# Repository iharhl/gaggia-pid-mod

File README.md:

# Gaggia PID mod

This project adds PID temperature control to my Gaggia Classic
espresso machine. Inspired by similar DIY efforts, I wanted to
challenge myself by designing and implementing the modification
entirely from scratch.

By default, Gaggia uses thermostat-based (on/off) temperature control,
which has noticed deviations from the ideal temperature. A PID controller
offers more precise and consistent temperature regulation compared to the
stock thermostat, which helps improve shot quality.

---

**Update Jul 2026:** I decided to create a custom "carrier" PCB which is more
compact, robust, and makes wiring more organized. Instead of using the same
microcontroller board, I switched from Pi Pico to RP2040-Zero (has the same MCU).
This readme file was updated accordingly. See the new control box below.

---

## Table of contents

1. [Hardware](#hardware)
   - [Temperature sensing](#temperature-sensing)
   - [Power switching](#power-switching)
   - [Microcontroller board](#microcontroller-board)
   - [Additional hardware](#additional-hardware)
   - [Bonus: Brew timer](#bonus-brew-timer)
2. [Software](#software)
   - [Temperature measurement](#temperature-measurement)
   - [PID controller](#pid-controller)
   - [Relay control](#relay-control)
   - [Error handler](#error-handler)
   - [Display](#display)
   - [Pump](#pump)
   - [Other](#other)
   - [Helper tools](#helper-tools)
3. [Results](#results)
   - [Calibration](#calibration)
   - [Final assembly (old)](#final-assembly-old-pi-pico-version)
   - [Final assembly (new)](#final-assembly-new-rp2040-zero-version)
   - [Taste Test](#taste-test)
4. [Resources](#resources)

## Hardware

The Gaggia machine regulates temperature using basic thermostat, which
functions as a switch that cuts off power when the water temperature
exceeds its rated threshold – 107°C for brewing. However, this approach
results in a sluggish system response. Once the temperature reaches the
cutoff point, it tends to slowly oscillate around the target, deviating
by several degrees. This rudimentary control method lacks the precision
needed for accurate temperature regulation.

To achieve more precise control, we need to continuously monitor the
water temperature and adjust the power to the heating element dynamically
based on real-time measurements. This allows for smoother and more
accurate temperature control.

To implement such a system, following components are required:

- Temperature sensor
- Power switch
- Microcontroller board

### Temperature sensing

The application requires measuring relatively short-term changes in
temperature over a wide range (~0°C to 200°C) with high accuracy
(better than ±0.5°C).

A common use case that fits these requirements is temperature control
in a water heater, where RTD (Resistance Temperature Detector) sensors
are frequently used. For this purpose, a Pt100 RTD sensor was
selected. It meets the accuracy and range specifications and is readily
available with an M4 adapter suitable for mounting to a boiler.

However, achieving accurate temperature readings from an RTD sensor
requires a precise analog-to-digital converter (ADC) and amplification.
Fortunately, this problem has been effectively solved with the MAX31865
– a user-friendly resistance-to-digital converter optimized for platinum
RTDs like the Pt100. With the MAX31865, you simply connect the sensor,
configure the device, and it provides accurate digital temperature
readings.

Adafruit offers high-quality breakout boards based on the MAX31865
chip, along with comprehensive documentation and example code. The sensor
itself I found on AliExpress with integrated M4 screw and of 3-wire type.
See examples of MAX31865 and RTD sensor below.

### Power switching

With the thermostat removed, an alternative method is needed to switch
the power on and off. A mechanical relay is the most straightforward
option and probably could suffice.

However, solid-state relays (SSRs) are often preferred in high-power
scenarios for several practical reasons. While both options are capable
of handling the load, SSRs offer significant advantages:

- Silent operation: unlike mechanical relays that produce an audible
"click" during switching, SSRs operate silently.

- Longer lifespan: SSRs have no moving parts, which drastically reduces
mechanical wear and increases operational longevity, particularly under
frequent switching conditions.

- Faster switching: the ability of SSRs to switch much faster than
mechanical relays.

- Reduced electrical noise: SSRs can be zero-crossing triggered, 
minimizing electrical noise and transients during switching.

Given these benefits, I opted for a commonly available 40A-rated SSR.
These are widely used, reliable, and relatively inexpensive, making
them a solid choice for high-power switching applications. According
to the specifications, the control method is listed as zero-crossing.
The SSR model is shown on the image below.

### Microcontroller board

There are many microcontrollers that could handle this task, as long as
they provide enough GPIO pins, support both I2C and SPI communication,
and have sufficient memory resources.

I had a Raspberry Pi Pico on hand that I hadn’t worked with before, so
I decided to use it as the microcontroller for this project.

**Update Jul 2026:** for a carrier PCB, I switch the board to RP2040-Zero –
both are supported now.

### Additional hardware

The components mentioned above cover the core functionality, but a few
important elements are still missing.

First, the Raspberry Pi Pico needs a power source. While it can be
powered via USB during development and debugging, this is only a
temporary solution. For a standalone setup, an AC/DC power supply is
required to draw power from the machine itself. I found a small module
on AliExpress that outputs up to 600mA at 5V, which is more than
sufficient for powering the Pico and a few peripherals.

The module turned out to be of poor quality. Its output was quite noisy,
and there were grounding issues. While most components in the system
would tolerate these, the MAX31865 is considerably more sensitive. As a
result, it frequently reported faults during temperature readings.

Fortunately, I had an AC/DC power supply from my broken speakers on hand,
so I used it for this project. Adding a pair of decoupling capacitors to
its output (100µF electrolytic and 0.1µF ceramic) resulted in a very smooth
voltage curve. However, the output measured at ~6V, which is around absolute
maximum rating of the on-board regulator. I used a diode to introduce a
voltage drop. Additionally, the power supply discharged very slowly after
the power was cut off. To address this, I soldered in a low-value bleed
resistor to speed up the discharge. In the end, the Pico is powered via
the VSYS pin with a stable ~5.1V supply.

Second, we need a way to monitor the machine's temperature in real
time. A small display would be a practical addition for this purpose,
allowing for quick and convenient observation of temperature readings.
I came across a very nice 1.5" 128×128 grayscale OLED display from
Adafruit, which includes comprehensive documentation.

### Bonus: Brew timer

Regarding the hydraulics upgrade, one of the most popular modifications
is the dimmer mod. This approach controls the pump flow by chopping the
AC supply using a phase-angle dimmer circuit. While it allows for
pressure profiling, it is worth noting that this method can lead to
increased wear on the pump, as this vibration pump is not designed to
operate under such conditions.

A simpler alternative is pump time control. By interrupting power to the
pump, you can implement programmable shot timing – effectively automating
brew durations without modifying flow or pressure directly. All that is
required for this mod is a relay board and some wiring to detect when the
brew button has been pressed.

Since I dragged this project out for too long, I ultimately decided
to skip the relay part of the mod – it would not have made a meaningful
difference for my use case anyway. However, I wired the brew button
to the Pico.

On the EU model of the machine, there is a switch-off board
included. Wires on the left side of the brew switch (in my case, blue and
green ones) are connected to it so that the power-off timer is reset
when brewing. I removed these two wires and shorted them (to make the
board think the brew is on at all time). The available connections can
now be used to detect when the button is pressed.

## Software

Since the Pico board was chosen, the MCU provides plenty of resources to
write a somewhat abstract code :)

To make the implementation easier to write and more readable, I followed
an OOP approach. Each component with a specific purpose is encapsulated
in its own class. For example, each communication protocol (I2C/SPI) is
implemented as a separate class. The drivers for external components,
such as MAX31865 and the OLED display, are also organized into classes
that utilize the I2C or SPI class instances for communication.

Here is a high-level overview of the software:

### Temperature measurement

Temperature measurements are obtained via the MAX31865 chip, which
uses SPI for communication. Hence, the SPI driver class was implemented.
Due to specific timing requirements of the MAX31865, slight modification
were done to the native Pico SDK SPI calls. The details are available in 
the implementation file – [src/spi.cpp](src/spi.cpp). Below are examples of
SPI read and write operations captured with a logic analyzer:

The MAX31865 driver implements the chip-specific logic
and utilizes the SPI class instance for communication. Details can be
found here – [src/max31865.cpp](src/max31865.cpp)

### PID controller

Not much to explain here – a PID temperature controller logic is
encapsulated within the PID class. The implementation is minimal, only
includes basic P-I-D action, no filtering, and includes integral
anti-windup to prevent the accumulation of integral action (which is 
important in such slow control systems).

The PID compute method takes temperature setpoint and the measurement as
inputs (error is calculated inside), and outputs the PWM percentage (duty
cycle). Implementation can be found here –
[src/pid.cpp](src/pid.cpp)

### Relay control

The SSR is controlled via PWM, hence the logic is put into PWM class.
The small problem here is that the control systems is quite slow
leading to a long PWM period, too long to be controlled using Pico's
dedicated PWM peripherals. Therefore, the PWM logic was implemented
via combination of timer peripheral and GPIO actions. Check details here –
[src/pwm.cpp](src/pwm.cpp)

<small>

> An interesting consideration here is how much power is delivered to the
heating element during each PWM period. Here's what I mean: suppose
the PID controller outputs a 10% duty cycle. Depending on the length
of the PWM period, this 10% can represent different chunks of time –
for example, 0.11 sec.
> 
> In the EU, the AC mains frequency is 50 Hz, meaning each full AC cycle
lasts 20 ms. However, 0.11 sec is not an even multiple of
the AC period (0.11 / 0.02 = 5.5 cycles), so the PWM period slices
through the AC waveform at arbitrary points. As a result, depending on
exactly where in the AC cycle the PWM turns on or off, the average power
delivered can fluctuate between periods.
>
> To achieve more consistent power delivery, it is desirable to align the
PWM period so that it is an integer multiple of the AC cycle period – for
example, setting the PWM period to 2 seconds (100 full AC cycles). This
way, for any given duty cycle, the on-time will always correspond to a
whole number of complete AC periods, rather than cutting through the AC
waveform at arbitrary points. As a result, the average power delivered
becomes more predictable and stable.
>
> Of course, there are some caveats here, and the topic can get quite
technical – including issues like the non-ideal nature of mains
frequency, inrush current when switching at AC peaks, and other
electrical nuances. That said, these details are not critical for this
particular system in my opinion, especially since the SSR I chose
features zero-crossing control. Still, it's an interesting topic to
explore.

</small>

### Error handler

As this mod is not exactly stress-tested, some form of error handler was
logical to implement.

The approach I took was straightforward: during a cycle, the system
checks whether input conditions are met. If a condition fails and the
associated error has a higher priority than previously stored error, the
system stores the new error code. At the end of the loop, the following
actions are taken:

- Disable PWM output if the error is severe enough.

- Display the current error code. If no error is present, reset the
error status and re-enable the PWM.

Possible error codes are summarized in the table below:

| Error Code | Error Context | Description                                                                           |
|------------|---------------|---------------------------------------------------------------------------------------|
| P0         | Protection    | Watchdog just rebooted the MCU (execution will continue shortly)                      |
| P1         |               | VSYS ADC is not configured correctly                                                  |
| P2         |               | Over voltage detected on VSYS                                                         |
| P3         |               | Under voltage detected on VSYS                                                        |
| P4         |               | Boiler too hot (higher than typical steaming temperature)                             |
| P5         |               | Machine was running for too long                                                      |
| C0         | Communication | Error occurred during I2C communication                                               |
| C1         |               | SPI device seems to be disconnected                                                   |
| S0         | Sensing       | MAX31865 reports under/overvoltage                                                    |
| S1         |               | MAX31865 reports RTD input voltage is too low                                         |
| S2         |               | MAX31865 reports reference input voltage is too high                                  |
| S3         |               | MAX31865 reports reference input voltage is too low                                   |
| S4         |               | MAX31865 reports RTD resistance is lower than the configured low threshold            |
| S5         |               | MAX31865 reports RTD resistance is higher than the configured high threshold          |
| S6         |               | Abnormal / not realistic boiler temperature (without MAX31865 reporting faults)       |
| HI         | User info     | Warning to the user that boiler temperature above setpoint (does not disable the PWM) |
| LO         |               | Warning to the user that boiler temperature below setpoint (does not disable the PWM) |
| OK         |               | Boiler temperature close to setpoint and no errors detected                           |

Check the implementation here – [src/error.cpp](src/error.cpp)

### Display

The OLED display uses SSD1327 driver chip with I2C as the default
communication protocol. I chose to structure the display logic in
3 layers:

- The I2C driver class handles communication. The default timings in the
Pico SDK were sufficient, so no modifications were necessary. Check 
here – [src/i2c.cpp](src/i2c.cpp)

- The SSD1327 driver manages the logic for updating the display, such
as filling or clearing the screen, drawing specific regions, and more.
Implementation can be found here – [src/ssd1327.cpp](src/ssd1327.cpp)

- The GUI driver oversees the display layout, including how quickly the
display is updated and how individual numbers or letters correspond to
an actual pixel data. Source file – [src/gui.cpp](src/gui.cpp)

Image below shows the layout of 128x128 display:

It is split into three rows. These rows are:

1. Thermometer icon and three digit fields to show the temperature
of the boiler.
2. Status icon and two fields to show the status code. Error codes are 
represented as a letter and a number (except for HI/LO/OK status codes).
3. Cup icon and two digit fields to show the shot timer. When the brew
switch is pressed, the timer starts. After the button is released, the
timer remains visible for 5 seconds before automatically resetting to
zero. The cup icon changes if the brew timer is active.

Images below show examples of what can be displayed.

<small>

> All the icons, letters, and numbers were drawn by me using an online
> designer for pixel art – Pixilart. The original .pixil files, generated
> png images, etc. are stored in [docs/display/](docs/display)

</small>

### Pump

The pump logic is based on a simple state machine. When the brew button
is pressed, the normally closed (NC) relay remains inactive, allowing
the water to flow. After the programmed time elapses, the relay opens,
cutting the power to the pump. After the brew button is released by the
user, the relay returns to its default closed position. For details, see
– [src/pump.cpp](src/pump.cpp)

This setup enables precise shot timing without the need for manual
tracking of time. While I have not set up the relay part myself, I've
left the code in place.

The part of the code that is used though, is detection of brew button
presses. This enables real-time display of the shot extraction time.

### Other

Source code also includes:

- Clock class provides current uptime of the MCU in ms, sec, and min.
All the methods are static as the class does not need to be instantiated,
it just encapsulates the logic relevant to time. Check
[src/clock.cpp](src/clock.cpp)

- Led class controls the on-board LED. Same as clock, all methods are
static. Check [src/led.cpp](src/led.cpp)

- Vsys monitor class provides the ability to measure the voltage on VSYS line.
As the ADC handling is minimal in the software, I decided to not create a
separate class for it. Check [src/vses.cpp](src/vsens.cpp). **Update Jul 2026:**
custom PCB has a voltage divider, which PR2040-Zero uses to read VDC from
the AC/DC supply, instead of measuring VSYS line itself.

- Watchdog that reboots the MCU if it is not updated in a defined amount
of time. It has no class of its own, direct SDK calls are used.

- For debug and test data recording, custom print functions were
implemented. They communicate data over serial to a connected
computer. Check [src/myprint.h](src/myprint.h)

### Helper tools

To aid the development, I made several scripts which are stored in the
[tools/](tools) folder.

| Script          | Description                                                                     |
|-----------------|---------------------------------------------------------------------------------|
| flash.sh        | Build and flash the binary on the Pico or PR2040-Zero boards and print its size |
| listen.py       | Connect to serial port and record data transmitted from the Pico                |
| process-data.py | Parse and plot the temperature data recorded from serial                        |
| png-to-bytes.py | Convert png image into raw data to be displayed on the OLED                     |

## Results

### Calibration

To calibrate the PID, I began by recording performance data. The
graphs below show the final results I was able to achieve after some
calibration.

The boiler heat-up is quite smooth, reaching operating temperature in
about 100 seconds. The system seems slightly over damped, requiring some
effort to reach the final few degrees. Once at temperature, it oscillates
with a ±1°C deviation for a short while. Given the system's slow thermal
response, I consider this level of accuracy quite acceptable. By around
the 4-minute mark, the error narrows to about ±0.5°C and continues to
improve over time.

The result of a shot pull test is also shown below. During brewing, the
water temperature drops by almost 3°C. After, it overshoots by about
1.5°C but stabilizes relatively quickly, with full recovery achieved
within a minute.

Additionally, I tested how well my modification works with the stock
steam control. As expected, once the boiler was heated, I reset the
steam switch, and the temperature gradually decreased. After such a
prolonged (passive) cooling, the integral term accumulated significantly,
resulting in an initial temperature undershoot (visible at around the
600-second mark). However, within about one and a half minutes, the
controller compensated and returned the system to the setpoint.

While this is not a realistic usage scenario – doubt anyone would really
wait 10 minutes for the boiler to cool passively (while having the machine
on) – I conducted a more practical test next. After reaching steam
temperature, I manually dropped the temperature by flushing water. This
caused the temperature to fall below the setpoint, but the controller
responded quickly. Two factors contributed to the improved response:
first, the integral term had less time to accumulate error; second, the
steep drop triggered a strong derivative response. In this test, the
system recovered rapidly and stabilized efficiently.

Overall, the controller is stable, and the system's performance is more
than adequate for real-world use – substantially better than the stock
configuration. Although further PID tuning is possible, the current
setup delivers great results.

### Final assembly (old Pi Pico version)

The circuit diagram of the final assembly is shown below. It illustrates
how most of the components were wired together.

The photos below provide a rough overview of the assembly process. In
the first image, I have highlighted the main modification. Here is a
brief explanation of the numbered tags:

1. **Power Source** – Power is drawn from the machine using piggyback
   connectors, which are active when the main power switch is turned on.
2. **Power Supply Box** – Contains the AC/DC power supply and a small
   piece of protoboard with the necessary components soldered in.
3. **RTD Sensor** – Replaces the machine's original thermostat.
4. **Solid-State Relay (SSR)** – Its AC side is connected to the two
   wires that were previously attached to the brew thermostat.
5. **Brew Switch Wiring** – Two wires are connected to the brew switch
   to detect when it’s pressed. The original disconnected wires are shorted
   to prevent the switch-off board from shutting down the machine.
6. **Control Box** – Houses the Raspberry Pi Pico and the MAX31865.

In the second image, you can see the fully assembled machine. The display
is mounted in a case attached to the side of the machine.

### Final assembly (new RP2040-Zero version)

Updating the assembly in Jul 2026 resulted in a change of a circuit diagram. See
the updated version below. Noticeable differences are:

- The MCU board switched from Pi Pico to RP2040-Zero.
- Voltage divider circuit is no longer on-board – dedicated 22k/10k one is added
  to the custom PCB. Note that it would be better to put it after the capacitors,
  but still works okay as shown.

Same as in the previous chapter (old assembly), the photos below show how the new
assembly looks like. In the first image, the main modification are highlighted
with the same number order. The wiring looks way cleaner in the new version.

All the enclosures were updated (for the controller, AC/DC supply and display).
Screen's enclosure is now magnetically attached to the machine's body. I made
hollow standoffs and put few tiny (6x2mm) neodymium magnets there which keep the
screen securely attached to the machine.

### Taste test

Finally, let's talk about the coffee itself. As a not-so-hardcore coffee
enthusiast, here is my take on the stock machine. Even with specialty beans,
it produced only decent results, definitely better than your average
non-specialty cafe, but still nothing I would drink without milk. The espresso
often leaned too acidic, and not in a pleasant way. Once in a while, I would
even get a hardly drinkable shot (skill issue, gonna admit).

The quality of the shots I got while testing the mod were surprising. I
finally was able to taste those flavor "notes" that coffee influencers always
talk about. The acidity was still present, but now it felt balanced – bright,
not sharp – allowing more complex flavors to emerge.

Even more surprising is that in a test setup and very little effort put
into puck preparation, the espresso tasted substantially better than on
the stock machine.

## Resources

Material on how to approach the mod:
- Gaggiuino project - https://gaggiuino.github.io/#/
- BaristaGadgets kit, specifically this video - https://www.youtube.com/watch?v=gj9qLIDaF9g
- Guide on how Gaggia machine works - https://comoricoffee.com/en/gaggia-classic-pro-circuit-diagram-en/

Example code from Adafruit for drivers development:
- MAX31865:
  - https://github.com/adafruit/Adafruit_MAX31865/tree/master
- SSD1327:
  - https://github.com/adafruit/Adafruit_SSD1327/blob/master/Adafruit_SSD1327.cpp
  - https://github.com/adafruit/Adafruit-GFX-Library/blob/master/Adafruit_GrayOLED.cpp

MAX31865 setup guide:
- https://learn.adafruit.com/adafruit-max31865-rtd-pt100-amplifier/overview

SSD1327 display setup guide:
- https://learn.adafruit.com/adafruit-grayscale-1-5-128x128-oled-display/overview

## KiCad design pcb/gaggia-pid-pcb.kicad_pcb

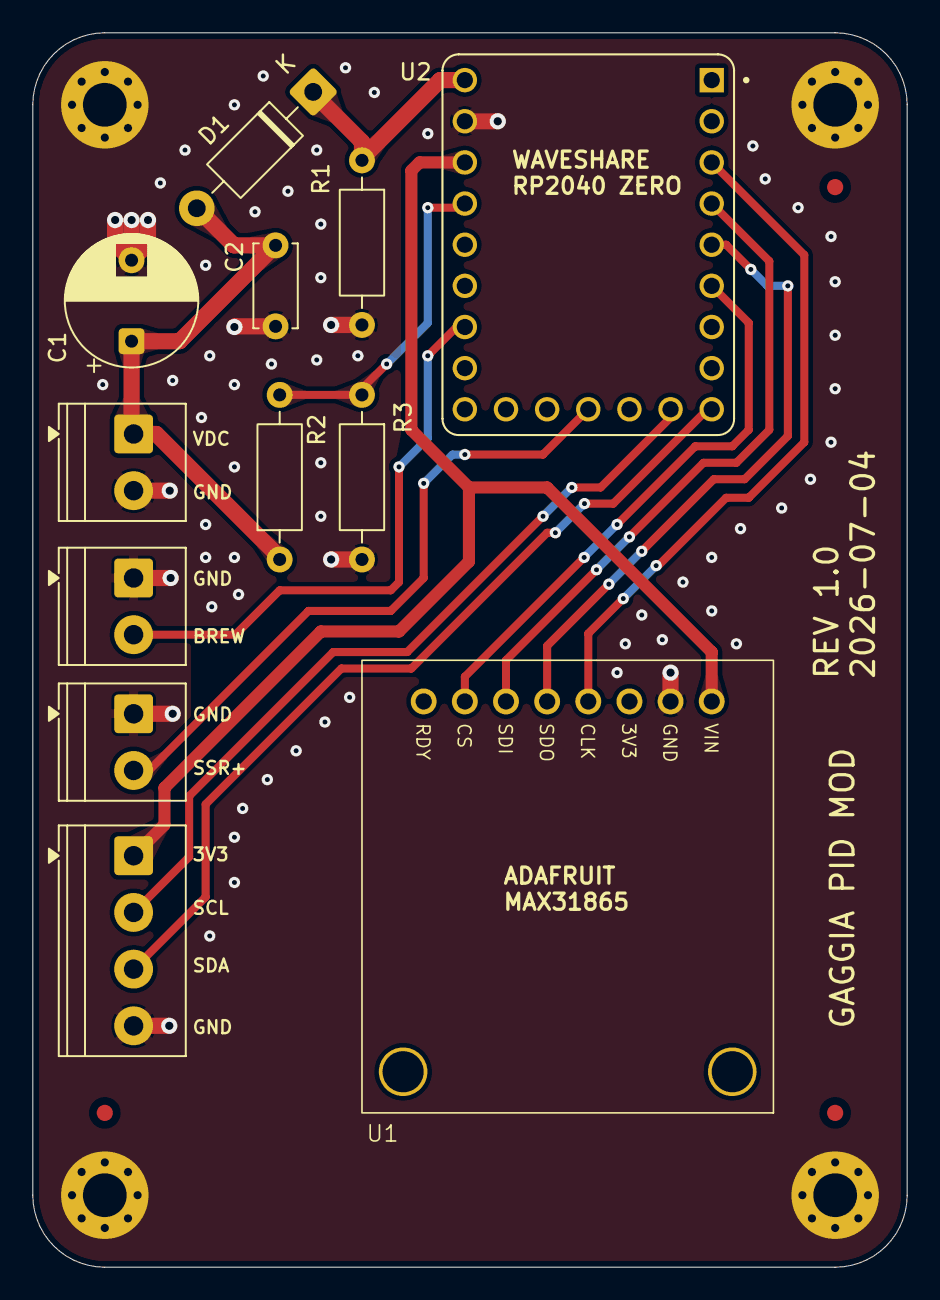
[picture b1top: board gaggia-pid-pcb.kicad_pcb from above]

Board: 2 copper layers, 54.0 x 76.2 mm, 19 parts (0 on the bottom side), 13 nets.

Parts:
C1: 100uF; CP_Radial_D8.0mm_P5.00mm
C2: 100nF; C_Disc_D5.0mm_W2.5mm_P5.00mm
D1: 1N47xxA; D_DO-41_SOD81_P10.16mm_Horizontal
FM1, FM2, FM3: Fiducial; Fiducial_1mm_Mask2mm
J1: Conn_01x04; TerminalBlock_Phoenix_PT-1,5-4-3.5-H_1x04_P3.50mm_Horizontal
J2, J3, J4: Conn_01x02; TerminalBlock_Phoenix_PT-1,5-2-3.5-H_1x02_P3.50mm_Horizontal
MH1, MH2, MH3, MH4: M3; MountingHole_2.7mm_M2.5_Pad_Via
R1: 1k; R_Axial_DIN0207_L6.3mm_D2.5mm_P10.16mm_Horizontal
R2: 22k; R_Axial_DIN0207_L6.3mm_D2.5mm_P10.16mm_Horizontal
R3: 10k; R_Axial_DIN0207_L6.3mm_D2.5mm_P10.16mm_Horizontal
U1: Adafruit MAX31865; Adafruit_MAX31865
U2: RP2040-ZERO

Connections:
+3.3V: J1.1, U1.1 (VIN), U2.21 (3V3)
+5V: D1.1 (K), R1.1, U2.23 (5V)
ADC3_VSENS: R2.2, R3.1, U2.20 (GP29)
GND: C1.2, C2.2, J1.4, J2.1, J3.1, J4.2, MH1.1 (1_1), MH2.1 (1_1), MH3.1 (1_1), MH4.1 (1_1), R1.2, R3.2, U1.2 (GND), U2.22 (GND)
GPIO_BREW_SW: J3.2, U2.17 (GP26)
GPIO_SSR: J2.2, U2.12 (GP11)
I2C0_SCL: J1.2, U2.10 (GP9)
I2C0_SDA: J1.3, U2.9 (GP8)
SPI0_CS: U1.7 (CS), U2.6 (GP5)
SPI0_MISO: U1.5 (SDO), U2.5 (GP4)
SPI0_MOSI: U1.6 (SDI), U2.4 (GP3)
SPI0_SCK: U1.4 (CLK), U2.3 (GP2)
VDC: C1.1, C2.1, D1.2 (A), J4.1, R2.1

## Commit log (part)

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2024-10-13 Setup project and added pid class
2024-12-26 Added MAX31865 driver
2024-12-26 Added spi driver class
2024-12-28 Added led class and fault detection
2024-12-28 Added temp calculation
2024-12-31 Corrected spi driver + added docs dir
2025-01-01 Implemented main loop + polishing stuff up
2025-01-01 Separated the ssr latch drive logic into pwm driver + moved time related methods into timer class
2025-01-02 Updated pwm pin drive action + pid dT time obtainment
2025-01-04 Added i2c driver + minor fixes around the code
2025-01-04 Added ssd1327 display driver
2025-01-05 Added display manager class + code refactoring
2025-01-05 Fixed bug with display init
2025-01-05 Fixed image of number 4
2025-01-07 Created error handler class + added files to docs
2025-01-08 Updates in error handler and display manager + minor renames/cosmetic changes
2025-01-08 Updates in error handling/displaying
2025-01-08 Removed/related some outdated display related docs
2025-01-09 Simplified status/error reporting + added some docs
2025-01-11 Changes: 1) Changed board to non-W version, 2) Added pump control logic, 3) Removed rough temp calc as not consistent for diff sensors, 4) Few other minor fixes
2025-03-22 Updated HW section of readme
2025-04-27 Major code refactoring, bugfixes and documentation changes after HIL testing
2025-04-28 Further refinements and bugfixes based on HIL testing
2025-04-30 Polished up code, tools and documentation (in progress)
2025-04-30 Trying to fix images displayed in readme
2025-04-30 Small formatting of readme
2025-05-01 Updated flash shell script
2025-05-01 Added brew time display functionality
2025-05-01 Updated testing data and readme
2025-05-01 Update in documentation
2025-05-01 Updated software arch image and put it into readme
2025-05-01 Fixed all warning, fixed some comments, etc.
2025-05-01 Switched from vector to malloc/calloc to reduce binary size
2025-05-02 Fixed led bugs
2025-05-02 Improved error reporting + polishing the code
2025-05-02 Changed the way how comm errors are obtained (esp SPI); update brewing icon (changes on brew); few minor corrections
2025-05-02 Updated display documentation + one bugfix in update cut icon
2025-05-04 Bugfixed/polishing after another round of testing
2025-05-06 Polishing up code + new tests + new section in readme
2025-05-07 Changes - 1) more error checks including Vsys monitoring, overheating and max runtime; 2) added watchdog; 3) small ssd1327 driver and gui handling improvements; 4) other code polishing
2025-05-09 Final improvements and test results after some more calibration. Updated readme.
2025-05-15 Minor polishing
2025-05-18 Updated final assembly in the readme and added the pictures
